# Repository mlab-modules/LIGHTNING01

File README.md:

# LIGHTNING01A

## Digital lightning sensor

Lightning sensor module based on [AS3935](https://cz.mouser.com/pdfdocs/AMS_AS3935_Datasheet_v4.pdf) Franklin Lightning Sensor IO. Sensor can be connected via I2C or SPI bus.

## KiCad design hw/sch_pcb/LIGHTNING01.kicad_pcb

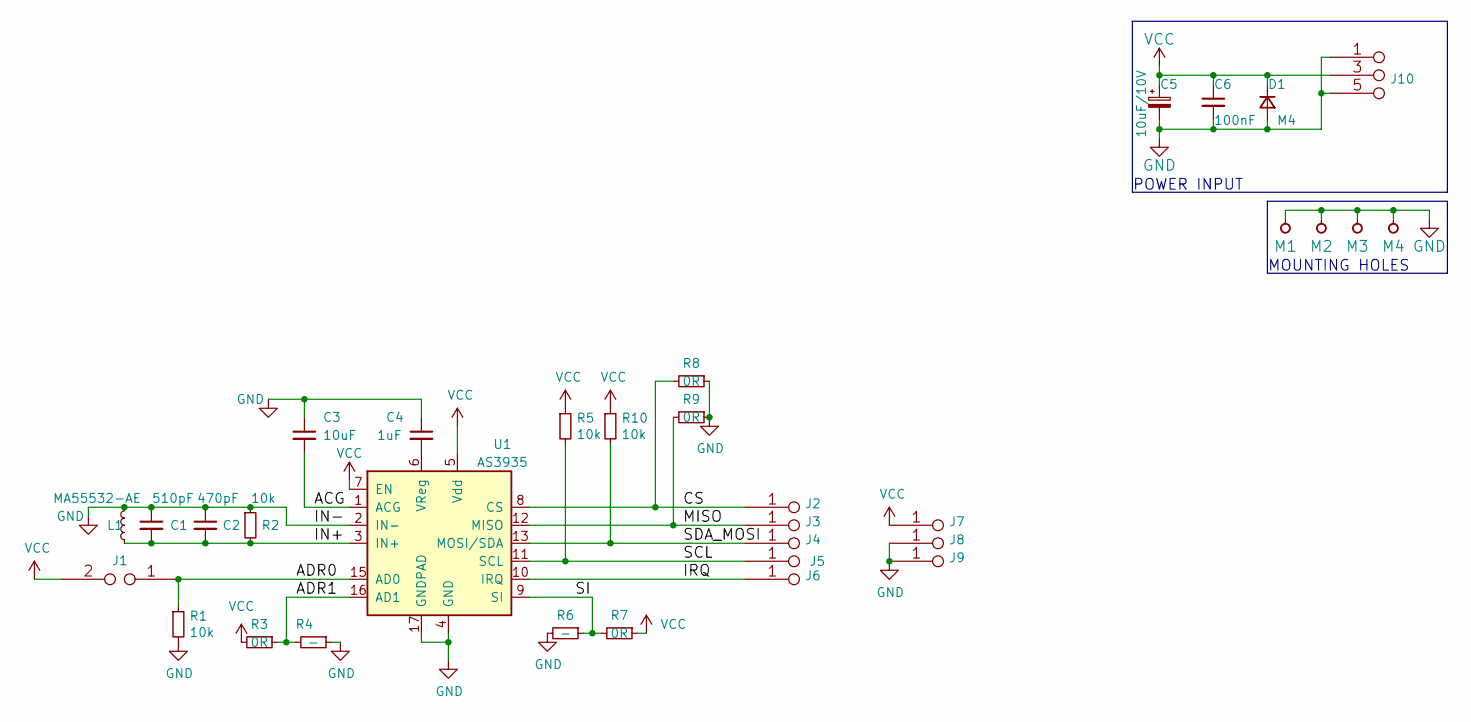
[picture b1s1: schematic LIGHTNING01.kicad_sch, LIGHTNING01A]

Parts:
C1: 510pF; SMD-0805
C2: 470pF; SMD-0805
C3: 10uF; SMD-0805
C4: 1uF; SMD-0805
C5: 10uF/10V; SMD-0805
C6: 100nF; SMD-0805
D1: M4; Diode-MELF_Standard
J1: JUMP2_2x1; Straight_2x01
J2, J3, J4, J5, J6, J7, J8, J9: JUMP_2x1; Straight_2x01
J10: JUMP_3X2; Straight_2x03
L1: MA55532-AE; Coilcraft_MA5532-AE_RFID
M1, M2, M3, M4: HOLE; MountingHole_3mm
R1, R2, R5, R10: 10k; SMD-0805
R3, R7, R8, R9: 0R; SMD-0805
R4, R6: -; SMD-0805
U1: AS3935; MLPQ-16

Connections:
/ACG: C3.2, U1.1 (ACG)
/ADR0: J1.1, R1.1, U1.15 (AD0)
/ADR1: R3.1, R4.2, U1.16 (AD1)
/CS: J2.1, J2.2, R8.2, U1.8 (CS)
/IN+: C1.2, C2.2, L1.1, R2.2, U1.3 (IN+)
/IRQ: J6.1, J6.2, U1.10 (IRQ)
/MISO: J3.1, J3.2, R9.2, U1.12 (MISO)
/SCL: J5.1, J5.2, R5.2, U1.11 (SCL)
/SDA_MOSI: J4.1, J4.2, R10.2, U1.13 (MOSI/SDA)
/SI: R6.1, R7.2, U1.9 (SI)
GND: C1.1, C2.1, C3.1, C4.1, C5.2, C6.2, D1.2 (A), J8.1, J8.2, J9.1, J9.2, J10.1 (2), J10.2, J10.5 (6), J10.6, L1.2, M1.1, M2.1, M3.1, M4.1, R1.2, R2.1, R4.1, R6.2, R8.1, R9.1, U1.2 (IN-), U1.4 (GND), U1.17 (GNDPAD)
unnamed: C4.2, U1.6 (VReg)
VCC: C5.1, C6.1, D1.1 (K), J1.2, J7.1, J7.2, J10.3 (4), J10.4, R3.2, R5.1, R7.1, R10.1, U1.5 (Vdd), U1.7 (EN)

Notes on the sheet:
MOUNTING HOLES
POWER INPUT

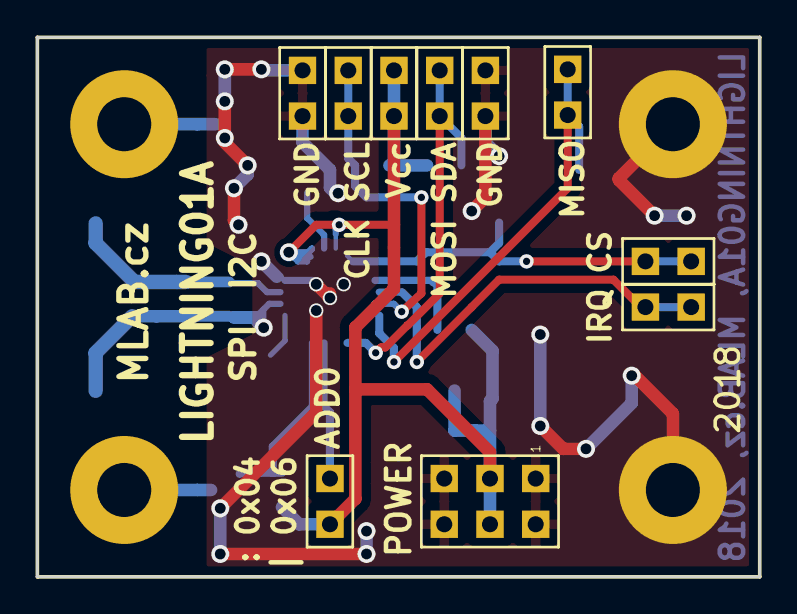
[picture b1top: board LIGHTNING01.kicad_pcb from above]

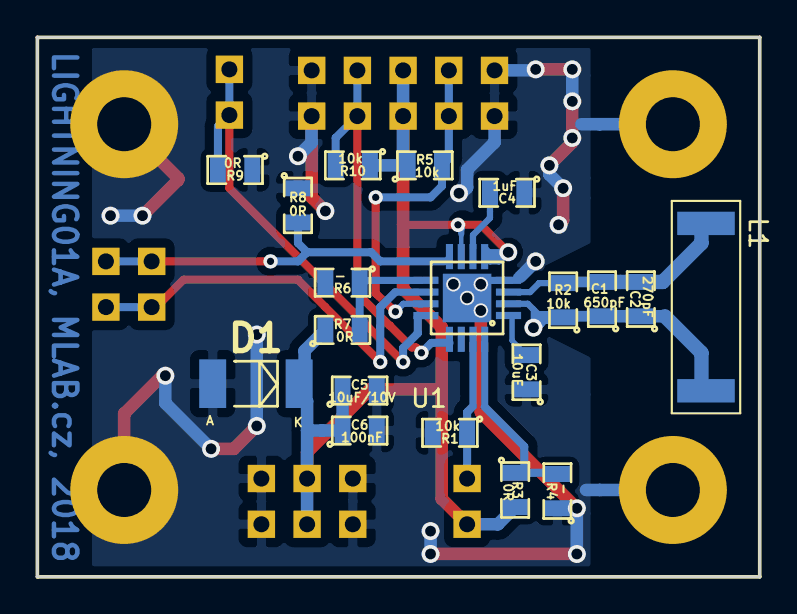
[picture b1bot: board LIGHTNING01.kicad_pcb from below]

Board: 2 copper layers, 40.1 x 30.0 mm, 33 parts (19 on the bottom side), 13 nets.

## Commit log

2023-04-01 Adding force option to enable splitting in not fresh copy of Modules repository.
2023-05-25 submodule
2023-05-25 Update metadata files
2023-05-26 repair WB, update metadata
2023-05-26 clean repo, update project files to kicad 6
2023-05-26 update actions
2023-05-26 Update actions products
2023-05-28 Update workflow files
2023-05-28 automated commit; add github actions
2023-07-05 automated commit; rename source files to new naming convence
2023-09-16 Update status
